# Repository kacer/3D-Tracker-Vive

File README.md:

# 3D Tracker compatible with HTC Vive
This little device is capable of tracking its position in the world. The tracked position is then sent over BLE to the smartphone. The [mobile app](https://github.com/kacer/3D-Tracker-Vive-Android) was created for this purpose and renders the positions of all connected 3D trackers. For tracking 3D Tracker uses two HTC Base Stations which are part of the HTC Vive set for VR. For now, the tracker uses HTC Base Station 1.0 but HW is ready for HTC Base Station 2.0. This project came to the world within my master's thesis. The idea of position calculation is based on repo [vive-diy-position-sensor](https://github.com/ashtuchkin/vive-diy-position-sensor). 

The dimensions of the 3D tracker are 6.3x4.7 cm and can be worn like a watch. The 3D tracker itself looks: 
|  |  |
| --- | --- |

The demo of position tracking by two 3D trackers on YouTube:

## Hardware
The 3D tracker is based on **nRF52840** and uses as a sensor of IR light **TS4231 + photodiode BPW34S**. For now, only one sensor is used and thus calibration of positions of HTC Base Station must be taken from SteamVR through this utility [vive-diy-position-sensor-geometry-getter](https://github.com/ashtuchkin/vive-diy-position-sensor-geometry-getter). This utility prints to console the geometry of HTC Base Stations which is consists of position and rotation matrix. This data are then copied and save to txt file. After that, the txt file with geometry is copied to the smartphone and through the [mobile app](https://github.com/kacer/3D-Tracker-Vive-Android) is sent to 3D trackers. Because nRF52840 was used additional sensors are possible to add.

## Getting started
The firmware of 3D Tracker was written in [PlatformIO](https://platformio.org/) with Arduino framework in C++. I recommend using the Visual Studio Code for developing. The installation process of PlatfromIO is pretty simple. Just install it like an extension of the VS Code. Then clone this repository, open it in VS Code, build and upload to your board.

### Uploading firmware into board
I used a [development kit with nRF52840](https://www.nordicsemi.com/Software-and-Tools/Development-Kits/nRF52840-DK) from Nordic Semiconductor for burning firmware into a chip. Wiring was following:

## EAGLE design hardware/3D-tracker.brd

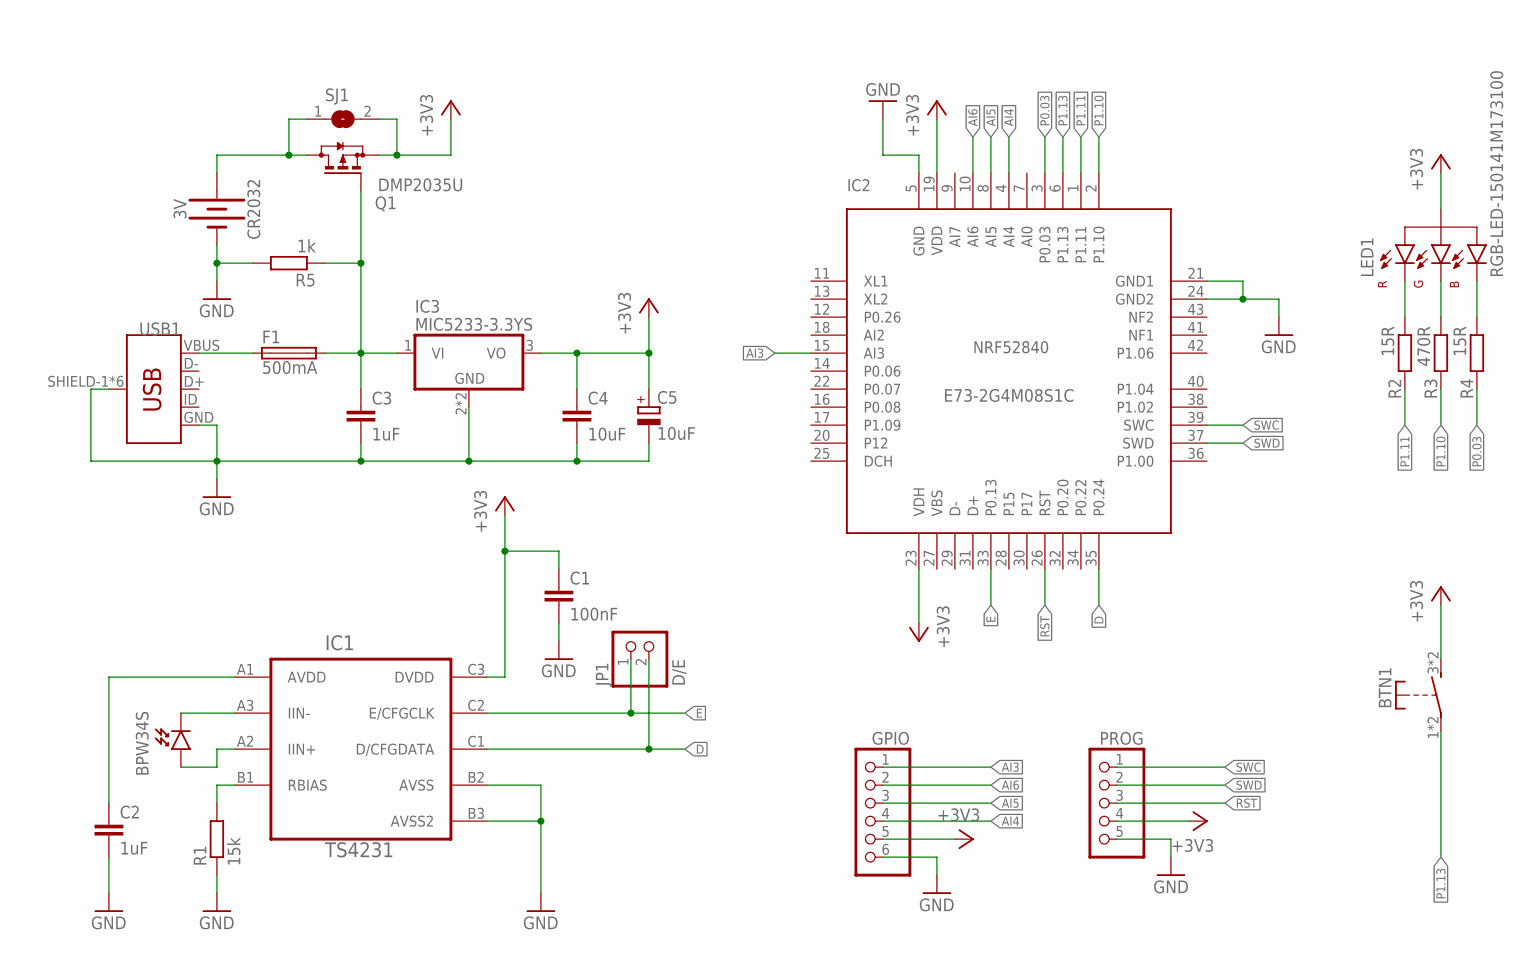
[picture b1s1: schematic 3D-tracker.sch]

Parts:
BPW34S: JONNEW_PHOTODIODE_VBPW34S; JONNEW_VBPW34S
BTN1: SWITCH-SMD
C1: 100nF; C0805
C2, C3: 1uF; C0805
C4: 10uF; C0805
C5: 10uF; E2-5
CR2032: 3V; BATTCON_20MM
F1: 500mA; R1206
GPIO: PINHD-1X6; 1X06
IC1: TS4231; JONNEW_WLCSP3X3
IC2: NRF52840; PE73(2G4M08S1C)
IC3: MIC5233-3.3YS; SOT223
JP1: D/E; 1X02
LED1: RGB-LED-150141M173100; LED4-3.5X2.8
PROG: PINHD-1X5; 1X05
Q1: DMP2035U; SOT23
R1: 15k; R0805
R2, R4: 15R; R0805
R3: 470R; R0805
R5: 1k; R0805
SJ1: SJ
USB1: USB-B-MICRO-SMD; MICRO-USB-B-SMD

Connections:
+3V: CR2032.1 (+), CR2032.3 (+), Q1.3 (D), SJ1.1
+3V3: BTN1.3 (S), BTN1.4 (S), C1.1, C4.1, C5.+, GPIO.5, IC1.C3 (DVDD), IC2.19 (VDD), IC2.23 (VDH), IC3.3 (VO), LED1.1 (ALL-A), PROG.4, Q1.2 (S), SJ1.2
+5V: C3.1, F1.2, IC3.1 (VI), Q1.1 (G), R5.1
AI3: GPIO.1, IC2.15 (AI3)
AI4: GPIO.4, IC2.4 (AI4)
AI5: GPIO.3, IC2.8 (AI5)
AI6: GPIO.2, IC2.10 (AI6)
AVDD: C2.1, IC1.A1 (AVDD)
D: IC1.C1 (D/CFGDATA), IC2.35 (P0.24), JP1.2
E: IC1.C2 (E/CFGCLK), IC2.33 (P0.13), JP1.1
GND: C1.2, C2.2, C3.2, C4.2, C5.-, CR2032.2 (-), GPIO.6, IC1.B2 (AVSS), IC1.B3 (AVSS2), IC2.5 (GND), IC2.21 (GND1), IC2.24 (GND2), IC3.2 (GND), IC3.4 (GND), PROG.5, R1.1, R5.2, USB1.GND, USB1.SHIELD-1 (SHIELD), USB1.SHIELD-2 (SHIELD), USB1.SHIELD-3 (SHIELD), USB1.SHIELD-4 (SHIELD), USB1.SHIELD-5 (SHIELD), USB1.SHIELD-6 (SHIELD)
IIN+: BPW34S.A, IC1.A2 (IIN+)
IIN-: BPW34S.C, IC1.A3 (IIN-)
unnamed: LED1.2 (BLUE-C), R4.1
unnamed: LED1.3 (RED-C), R2.1
unnamed: LED1.4 (GREEN-C), R3.1
P0.03: IC2.3 (P0.03), R4.2
P1.10: IC2.2 (P1.10), R3.2
P1.11: IC2.1 (P1.11), R2.2
P1.13: BTN1.1, BTN1.2, IC2.6 (P1.13)
RBIAS: IC1.B1 (RBIAS), R1.2
RST: IC2.26 (RST), PROG.3
SWC: IC2.39 (SWC), PROG.1
SWD: IC2.37 (SWD), PROG.2
VBUS: F1.1, USB1.VBUS

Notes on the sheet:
E73-2G4M08S1C

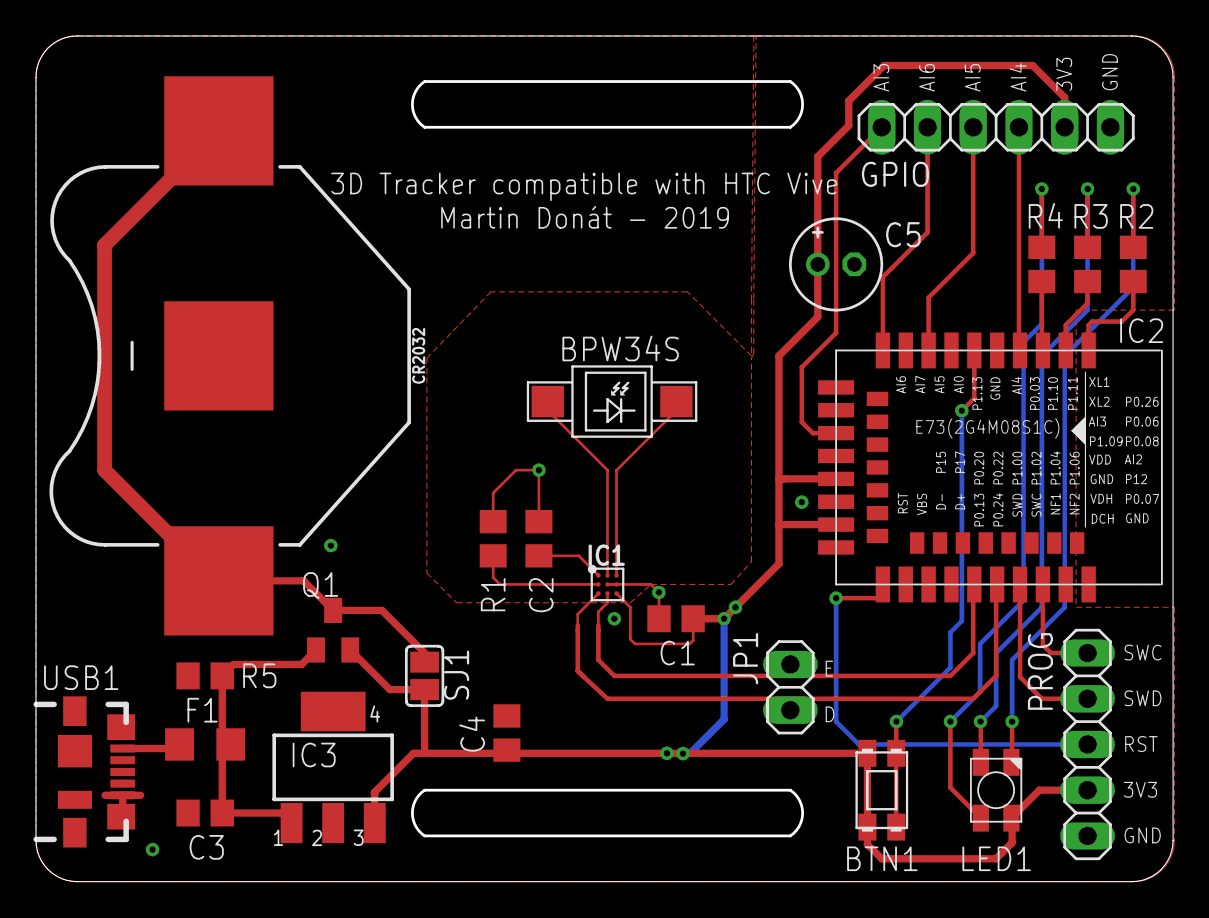
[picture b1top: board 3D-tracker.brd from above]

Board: 2 copper layers, 63.0 x 46.8 mm, 24 parts (0 on the bottom side), 25 nets.

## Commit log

2020-03-04 Initial commit - add hw design files, basic .gitignore config, empty source code
2020-03-14 Add calculation of angles between sensor and base stations
2020-03-23 Add implementation of position calculation from given angles
2020-03-24 Break off code for processing pulses into separate class which uses ring buffer
2020-03-24 Add Bluetooth LE functionality to project
    Had to change register CHEN to CHENSET for enabling PPI channels. Writing into CHEN register cause that other PPI channels will overwrite. Register CHENSET is safer, only set wanted bits.
2020-03-25 Fix bugs with sync pulses and computing 2 angles in one cycle
    Add code that checks every start of cycle with 2 sync pulses.
    Add check for sweep pulses inside of computeAngle function. Maybe could be better store every "sweep" pulse in array and at the end of cycle compute angle with maximum length of "sweep" pulse from ar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
2020-04-07 Add Bluetooth and led driver
    Contains debug prints
2020-04-09 Remove unused code
2020-04-24 Update electrical scheme, add gerber file, add hw images
2020-04-24 Remove debug prints, edit docs a little bit, some renames
2020-04-24 Set default pull-down for button to prevent accidental damage
2020-04-24 Add state showing geometry is not set at the start of program
2020-04-30 Rename zip with gerber files for clarification
2020-06-03 Add README.md file to repository
